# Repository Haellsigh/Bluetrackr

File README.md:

# Bluetrackr

Bluetrackr is a head tracking device. It allows you to track your head orientation & position in realtime. It's mainly used in games such as Elite Dangerous, Star Citizen, Flight simulators, etc to simulate head movement in a cockpit.

## Progress
prototype-v1: There was an unknown problem with the SPI bus. Might be because there are two devices on the same SPI bus?
prototype-v2: Ordered, waiting for parts.

Everything below is for v2.

### Transmitter schematic:

### Transmitter PCB:

### Transmitter PCB 3D view:

## Prototypes

#### Soldered prototype-v1

#### Board prototype-v2

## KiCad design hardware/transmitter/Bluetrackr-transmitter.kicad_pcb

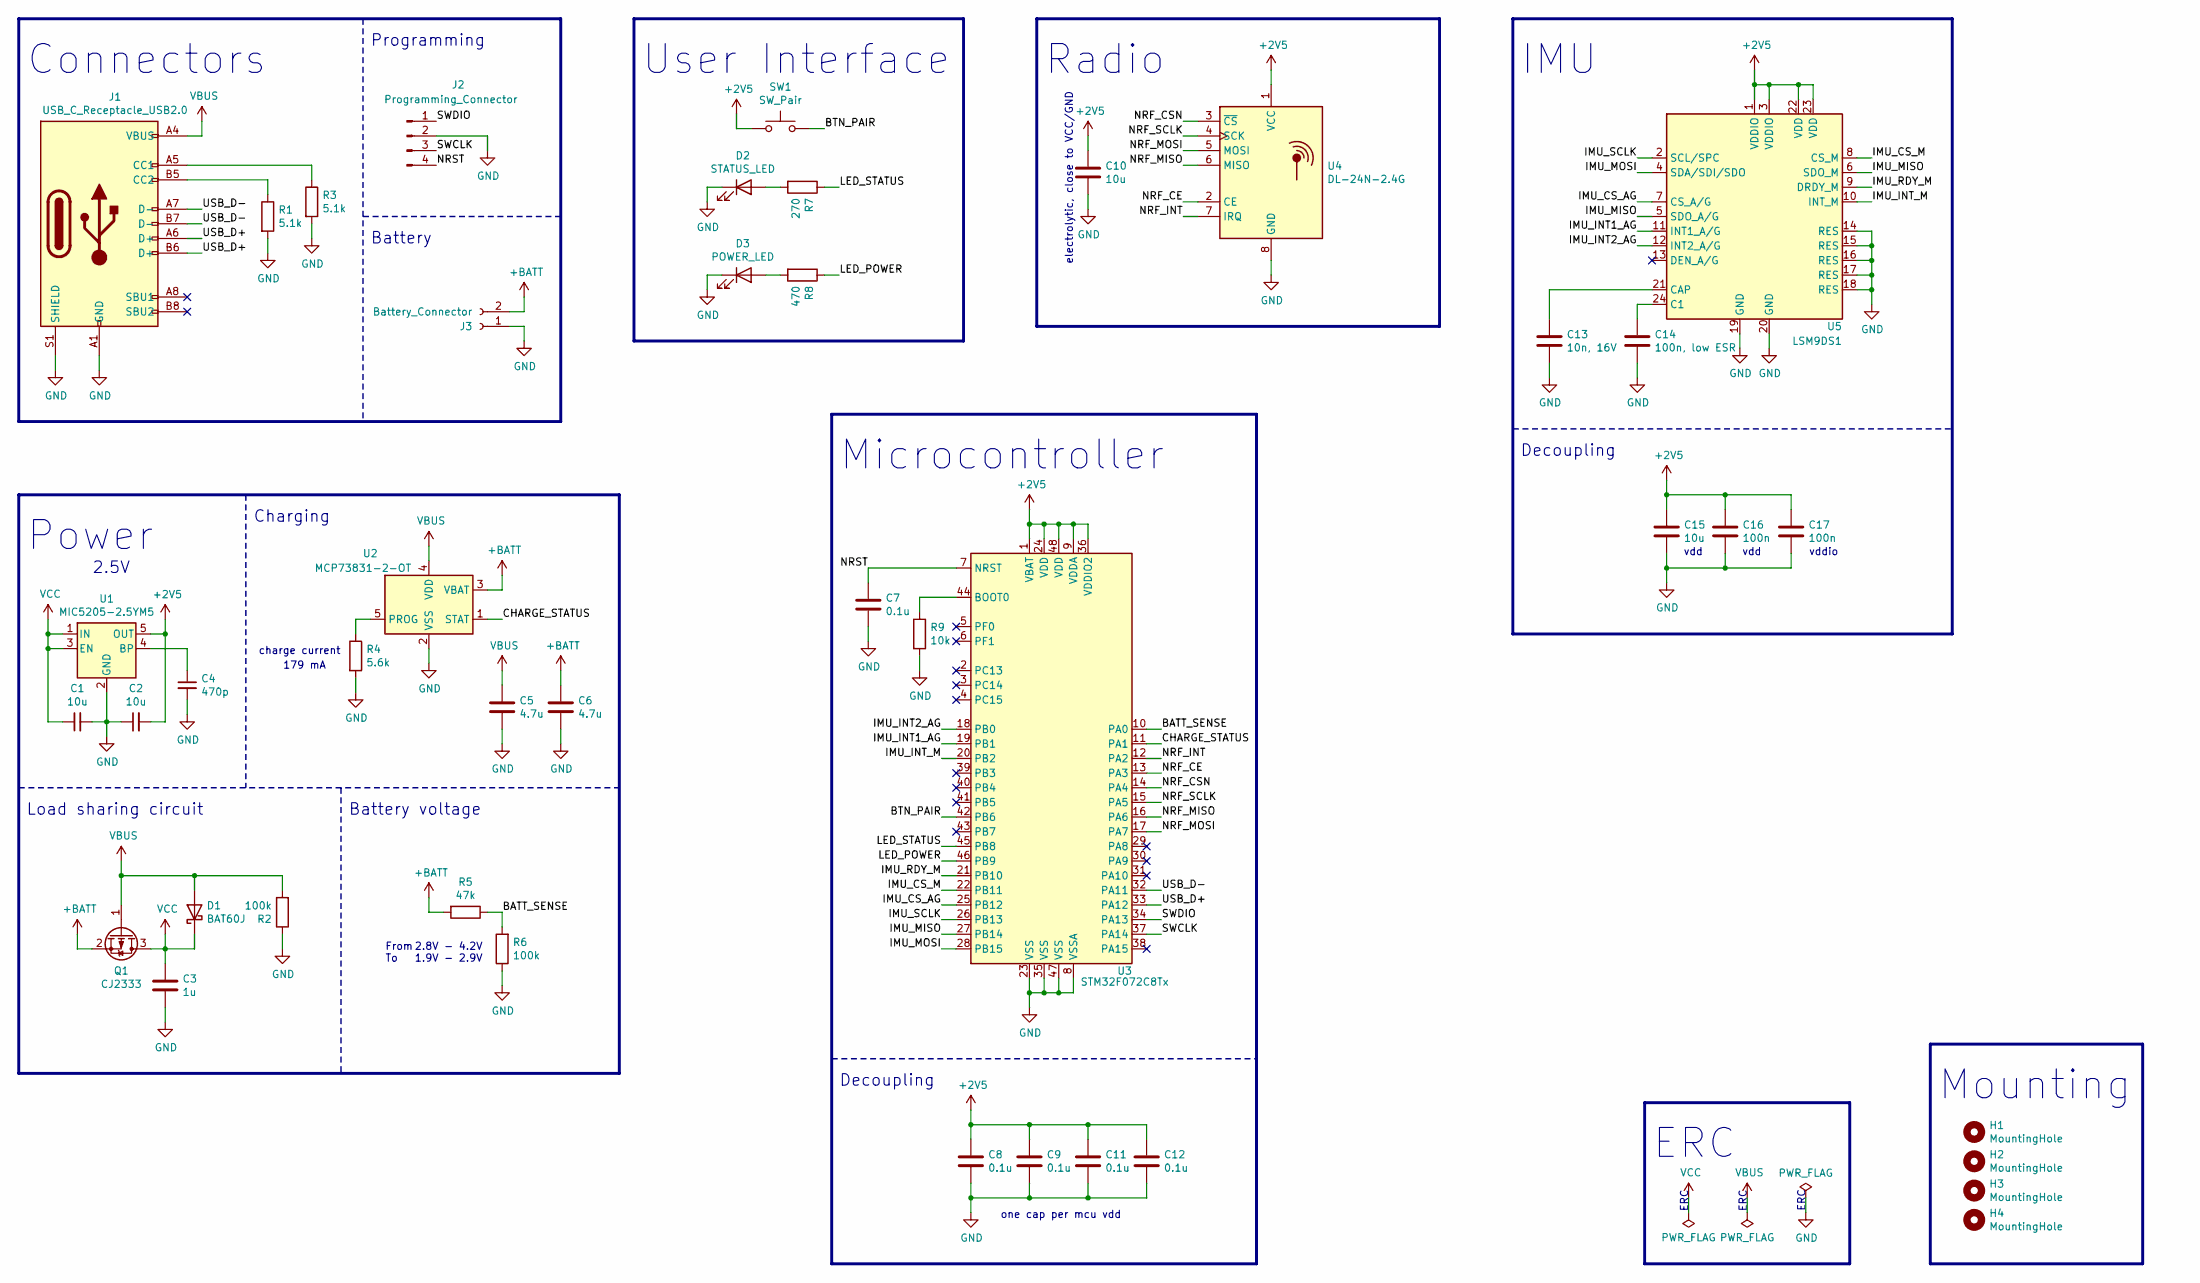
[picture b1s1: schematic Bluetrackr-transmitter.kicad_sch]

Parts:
C1, C2: 10u; C_0805_2012Metric_Pad1.15x1.40mm_HandSolder
C3: 1u; C_0805_2012Metric_Pad1.15x1.40mm_HandSolder
C4: 470p; C_0805_2012Metric_Pad1.15x1.40mm_HandSolder
C5, C6: 4.7u; C_0805_2012Metric_Pad1.15x1.40mm_HandSolder
C7, C8, C9, C11, C12: 0.1u; C_0805_2012Metric_Pad1.15x1.40mm_HandSolder
C10, C15: 10u; CP_Elec_3x5.3
C13: 10n, 16V; C_0805_2012Metric_Pad1.15x1.40mm_HandSolder
C14: 100n, low ESR; C_0805_2012Metric_Pad1.15x1.40mm_HandSolder
C16, C17: 100n; C_0805_2012Metric_Pad1.15x1.40mm_HandSolder
D1: BAT60J; D_SOD-323
D2: STATUS_LED; LED_1206_3216Metric_Pad1.42x1.75mm_HandSolder
D3: POWER_LED; LED_1206_3216Metric_Pad1.42x1.75mm_HandSolder
H1, H2, H3, H4: MountingHole; MountingHole_2.2mm_M2
J1: USB_C_Receptacle_USB2.0; USB_C_Receptacle_HRO_TYPE-C-31-M-12
J2: Programming_Connector; JST_B4B-ZR-SM4-TF
J3: Battery_Connector; JST_S2B-ZR-SM4A-TF
Q1: CJ2333; SOT-23
R1, R3: 5.1k; R_0805_2012Metric_Pad1.15x1.40mm_HandSolder
R2, R6: 100k; R_0805_2012Metric_Pad1.15x1.40mm_HandSolder
R4: 5.6k; R_0805_2012Metric_Pad1.15x1.40mm_HandSolder
R5: 47k; R_0805_2012Metric_Pad1.15x1.40mm_HandSolder
R7: 270; R_0805_2012Metric_Pad1.15x1.40mm_HandSolder
R8: 470; R_0805_2012Metric_Pad1.15x1.40mm_HandSolder
R9: 10k; R_0805_2012Metric_Pad1.15x1.40mm_HandSolder
SW1: SW_Pair; SW_PUSH_6mm_H9.5mm
U1: MIC5205-2.5YM5; SOT-23-5
U2: MCP73831-2-OT; SOT-23-5
U3: STM32F072C8Tx; LQFP-48_7x7mm_P0.5mm
U4: DL-24N-2.4G
U5: LSM9DS1; LGA-24L_3x3.5mm_P0.43mm

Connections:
+2V5: C2.2, C8.1, C9.1, C10.1, C11.1, C12.1, C15.1, C16.1, C17.1, SW1.1, U1.5 (OUT), U3.1 (VBAT), U3.9 (VDDA), U3.24 (VDD), U3.36 (VDDIO2), U3.48 (VDD), U4.1 (VCC), U5.1 (VDDIO), U5.3 (VDDIO), U5.22 (VDD), U5.23 (VDD)
+BATT: C6.1, J3.2, Q1.2 (S), R5.2, U2.3 (VBAT)
/BATT_SENSE: R5.1, R6.2, U3.10 (PA0)
/BTN_PAIR: SW1.2, U3.42 (PB6)
/CHARGE_STATUS: U2.1 (STAT), U3.11 (PA1)
/IMU_CS_AG: U3.25 (PB12), U5.7 (CS_A/G)
/IMU_CS_M: U3.22 (PB11), U5.8 (CS_M)
/IMU_INT1_AG: U3.19 (PB1), U5.11 (INT1_A/G)
/IMU_INT2_AG: U3.18 (PB0), U5.12 (INT2_A/G)
/IMU_INT_M: U3.20 (PB2), U5.10 (INT_M)
/IMU_MISO: U3.27 (PB14), U5.5 (SDO_A/G), U5.6 (SDO_M)
/IMU_MOSI: U3.28 (PB15), U5.4 (SDA/SDI/SDO)
/IMU_RDY_M: U3.21 (PB10), U5.9 (DRDY_M)
/IMU_SCLK: U3.26 (PB13), U5.2 (SCL/SPC)
/LED_POWER: R8.1, U3.46 (PB9)
/LED_STATUS: R7.1, U3.45 (PB8)
/NRF_CE: U3.13 (PA3), U4.2 (CE)
/NRF_CSN: U3.14 (PA4), U4.3 (~CS)
/NRF_INT: U3.12 (PA2), U4.7 (IRQ)
/NRF_MISO: U3.16 (PA6), U4.6 (MISO)
/NRF_MOSI: U3.17 (PA7), U4.5 (MOSI)
/NRF_SCLK: U3.15 (PA5), U4.4 (SCK)
/NRST: C7.1, J2.4, U3.7 (NRST)
/SWCLK: J2.3, U3.37 (PA14)
/SWDIO: J2.1, U3.34 (PA13)
/USB_D+: J1.A6 (D+), J1.B6 (D+), U3.33 (PA12)
/USB_D-: J1.A7 (D-), J1.B7 (D-), U3.32 (PA11)
GND: C1.2, C2.1, C3.2, C4.2, C5.2, C6.2, C7.2, C8.2, C9.2, C10.2, C11.2, C12.2, C13.2, C14.2, C15.2, C16.2, C17.2, D2.1 (K), D3.1 (K), J1.A1 (GND), J1.A12 (GND), J1.B1 (GND), J1.B12 (GND), J1.S1 (SHIELD), J2.2, J3.1, R1.2, R2.1, R3.2, R4.2, R6.1, R9.2, U1.2 (GND), U2.2 (VSS), U3.8 (VSSA), U3.23 (VSS), U3.35 (VSS), U3.47 (VSS), U4.8 (GND), U5.14 (RES), U5.15 (RES), U5.16 (RES), U5.17 (RES), U5.18 (RES), U5.19 (GND), U5.20 (GND)
unnamed: C4.1, U1.4 (BP)
unnamed: C13.1, U5.21 (CAP)
unnamed: C14.1, U5.24 (C1)
unnamed: D2.2 (A), R7.2
unnamed: D3.2 (A), R8.2
unnamed: J1.A5 (CC1), R3.1
unnamed: J1.B5 (CC2), R1.1
unnamed: R4.1, U2.5 (PROG)
unnamed: R9.1, U3.44 (BOOT0)
VBUS: C5.1, D1.2 (A), J1.A4 (VBUS), J1.A9 (VBUS), J1.B4 (VBUS), J1.B9 (VBUS), Q1.1 (G), R2.2, U2.4 (VDD)
VCC: C1.1, C3.1, D1.1 (K), Q1.3 (D), U1.1 (IN), U1.3 (EN)

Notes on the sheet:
Connectors
Power
Load sharing circuit
2.5V
Charging
179 mA
charge current
Battery voltage
Programming
Battery
From To
2.8V - 4.2V 1.9V - 2.9V
User Interface
Microcontroller
Decoupling
one cap per mcu vdd
Radio
electrolytic, close to VCC/GND
IMU
ERC
vdd
vddio
Mounting

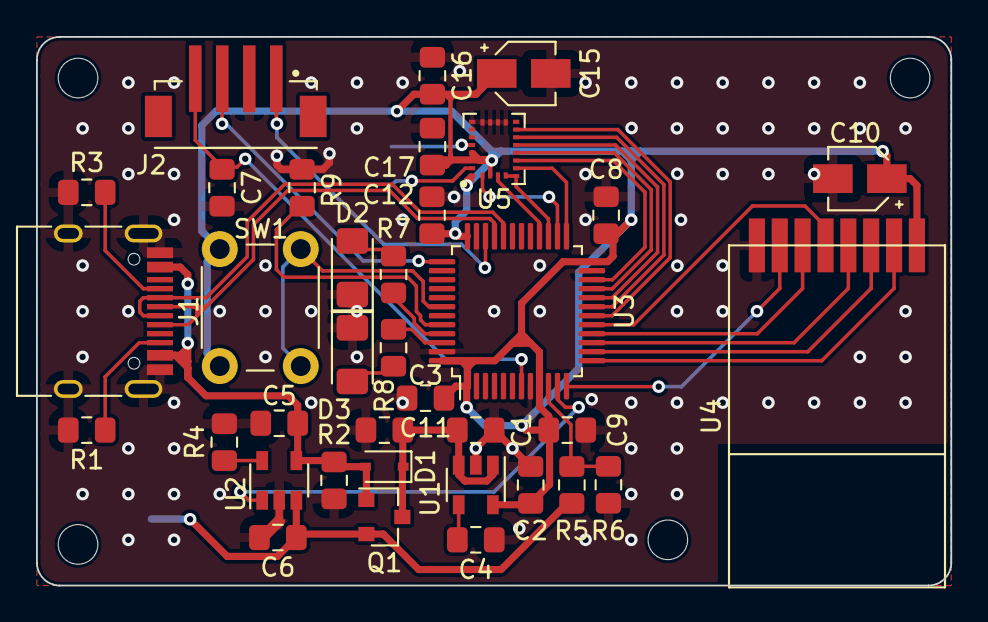
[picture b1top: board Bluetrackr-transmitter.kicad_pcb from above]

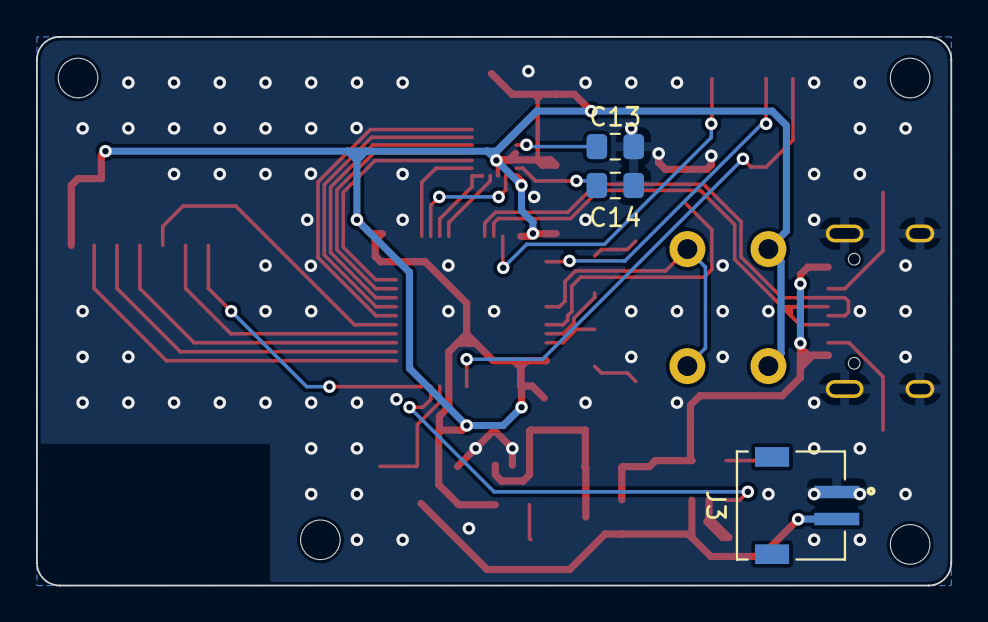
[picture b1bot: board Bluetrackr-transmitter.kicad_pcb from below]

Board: 2 copper layers, 50.8 x 30.5 mm, 43 parts (3 on the bottom side), 39 nets.

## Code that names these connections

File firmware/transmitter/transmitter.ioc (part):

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Mcu.Name=STM32F072C(8-B)Tx
Mcu.Package=LQFP48
Mcu.UserName=STM32F072C8Tx
PA0.GPIOParameters=GPIO_Label
PA0.GPIO_Label=BATT_SENSE
PA0.Mode=IN0
PA0.Signal=ADC_IN0
PA1.GPIOParameters=GPIO_Label
PA1.GPIO_Label=CHARGE_STATUS
PA1.Signal=GPIO_Input
PA11.Mode=Device
PA11.Signal=USB_DM
PA12.Mode=Device
PA12.Signal=USB_DP
PA13.Mode=Serial_Wire
PA13.Signal=SYS_SWDIO
PA14.Mode=Serial_Wire
PA14.Signal=SYS_SWCLK
PA2.GPIOParameters=GPIO_Label
PA2.GPIO_Label=NRF_INT
PA2.Signal=GPXTI2
PA3.GPIOParameters=GPIO_Label
PA3.GPIO_Label=NRF_CE
PA3.Signal=GPIO_Output
PA4.GPIOParameters=GPIO_Label
PA4.GPIO_Label=NRF_CSN
PA4.Signal=GPIO_Output
PA5.GPIOParameters=GPIO_Label
PA5.GPIO_Label=NRF_SCLK
PA5.Mode=Full_Duplex_Master
PA5.Signal=SPI1_SCK
PA6.GPIOParameters=GPIO_Label
PA6.GPIO_Label=NRF_MISO
PA6.Mode=Full_Duplex_Master
PA6.Signal=SPI1_MISO
PA7.GPIOParameters=GPIO_Label
PA7.GPIO_Label=NRF_MOSI
PA7.Mode=Full_Duplex_Master
PA7.Signal=SPI1_MOSI
PB0.GPIOParameters=GPIO_Label
PB0.GPIO_Label=IMU_INT2_AG
PB0.Signal=GPXTI0
PB1.GPIOParameters=GPIO_Label
PB1.GPIO_Label=IMU_INT1_AG
PB1.Signal=GPXTI1
PB10.GPIOParameters=GPIO_Label
PB10.GPIO_Label=IMU_RDY_M
PB10.Signal=GPIO_Input
PB11.GPIOParameters=GPIO_Label
PB11.GPIO_Label=IMU_CS_M
PB11.Signal=GPIO_Output
PB12.GPIOParameters=GPIO_Label
PB12.GPIO_Label=IMU_CS_AG
PB12.Signal=GPIO_Output
PB13.GPIOParameters=GPIO_Label
PB13.GPIO_Label=IMU_SCLK
PB13.Mode=Full_Duplex_Master
PB13.Signal=SPI2_SCK
PB14.GPIOParameters=GPIO_Label
PB14.GPIO_Label=IMU_MISO
PB14.Mode=Full_Duplex_Master
PB14.Signal=SPI2_MISO
PB15.GPIOParameters=GPIO_Label
PB15.GPIO_Label=IMU_MOSI
PB15.Mode=Full_Duplex_Master
PB15.Signal=SPI2_MOSI
PB6.GPIOParameters=GPIO_PuPd,GPIO_Label
PB6.GPIO_Label=BTN_PAIR
PB6.GPIO_PuPd=GPIO_PULLDOWN
PB6.Signal=GPIO_Input
PB8.GPIOParameters=GPIO_Label
PB8.GPIO_Label=LED_STATUS
PB8.Signal=GPIO_Output
PB9.GPIOParameters=GPIO_Label
PB9.GPIO_Label=LED_POWER
PB9.Signal=GPIO_Analog
RCC.SYSCLKFreq_VALUE=48000000
RCC.SYSCLKSource=RCC_SYSCLKSOURCE_PLLCLK
board=custom

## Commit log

2019-10-16 Add transmitter hardware project
2019-10-16 Remove pull down resistor on button
2019-10-16 Add base transmitter firmware project
2019-10-16 Ignore built files
2019-10-16 Finish transmitter schematic, pass DRC
2019-10-16 Layout the transmitter pcb
2019-10-16 Add progress images
2019-10-16 Add progress to README
2019-10-16 Update PCB rules
2019-10-16 Begin routing transmitter pcb
2019-10-17 Finished transmitter routing
2019-10-18 First working test: read MPU9250 values & output to serial
2019-10-25 Update firmware
2019-11-05 Begin receiver schematic
2019-11-21 Received, assembled, programmed the first working prototype of the transmitter
2019-11-24 Replace global labels with net labels
2019-11-24 Replace the unused programming pin with NRST to support stlink reset
2019-11-24 Updated changelog with commits
2019-11-27 Begin working on the blt library
2019-12-06 Moved the common libraries to a common folder
2019-12-06 Add hardware gitignore
2019-12-20 Add nRF24L01 v2 doc
2019-12-20 Fix nRF24 implementation a bit, still not working
2020-01-15 Hardware does not seem to work yet on the receiver side.
2020-01-17 Update transmitter schematic
2020-05-31 Use CMake to build the firmware
2020-06-02 Maybe it will work someday
2020-06-02 The current hardware doesn't seem to work
2020-06-04 Redesign most of the transmitter hardware
    Changes:
    - Switch to KiCad 6 files
    - Change microcontroller to STM32F030R8T6
    - Use two SPI buses, one for each device
    - Replace TP4056 module for a custom solution with:
    - USB Type-C USB 2.0 receptacle
2020-06-04 Remove changelog for now
2020-06-04 Fix not connected errors on ERC
2020-06-04 Update firmware and hardware gitignore
2020-06-04 Add board basic dimensions 5x3cm
2020-06-04 Rename schematic file
2020-06-04 Crop transmitter schematic
2020-06-04 Plot transmitter schematic again
2020-06-04 Update transmitter schematic pdf
2020-06-04 Change level shifting resistors to 10k
2020-06-04 Add transmitter schematic
2020-06-04 Changed regulator from 3.3V to 2.5V
2020-06-10 Began routing the pcb
2020-06-10 Replace nRF24 breakout with DL-24N nRF24 smd module
2020-06-10 Update hardware docs
2020-06-10 Replace ICM-20948 with LSM9DS1, removes 1.8V supply and level shifters
2020-06-10 Annotate schematic
2020-06-10 Remove pcb
2020-06-10 Finish schematic with new Radio & IMU
2020-06-10 Place mounting holes, usb connector, mcu and radio
2020-06-10 Setup board rules
2020-06-10 Move mounting holes silkscreen to fab layer
2020-06-10 Changed MCU to IMU pins
2020-06-10 Placed MCU and IMU
2020-06-10 Change MCU to STM32F072C8T6 for USB
2020-06-10 Reset and run bugged KiCad 5.99 ERC
2020-06-10 Add basic transmitter pcb with main ICs laid
2020-06-10 Place Power components
2020-06-11 Place CC1 and CC2 for USB
2020-06-11 Place LEDs
2020-06-11 Place BOOT0 resistor
2020-06-11 Change connectors to ZH SMD versions
2020-06-11 Add 3D models to JST ZH connectors
2020-06-11 Begin routing
2020-06-11 Routed USB, SPI tracks
2020-06-11 Finish routing the transmitter, add DL-24N module step file
2020-06-11 Correct some power traces
2020-06-11 Moved IMU interrupt lines further away
2020-06-11 Final PCB, ordered at JLCPCB
2020-06-11 Reset solder mask clearancec
2020-06-11 Plot gerbers and drill files
2020-06-11 Update plot settings
2020-06-12 Update schematic
2020-06-12 Update gitignores
2020-06-12 Update README images
2020-06-12 Remove ignored file
2020-06-12 Changed targets for testing to F303K8
2020-06-12 Switch target to F103 bluepill and add USB CDC
2020-06-14 Quick USB CDC test
2020-06-14 Begin removing CMake, use Platormio
2020-06-14 Add simple debug library for F303K8 via VCP UART
2020-06-14 Working PlatformIO integration
2020-06-14 Switched receiver to Platformio
2020-06-15 Fix nRF24 code on transmitter side
2020-06-18 Add transmitter board v1 and v2 images
2020-06-18 Update readme with prototypes
2020-06-18 Add goal
2020-06-20 Setup a typesafe register manipulation system entirely based on types
2020-06-26 Finish typesafe version prototype of the nRF24 library
2020-06-26 Fixed a pin toggling error in blt::gpio
2020-06-27 Working data transmission between a transmitter and a receiver
2020-06-27 Enable Usb Clock Recovery System (CRS) on the receiver side
2020-07-05 Commit before prototype programming
2020-07-07 Add HID joystick driver base
2020-07-07 USB HID custom virtual reality joystick with 3 axes implemented
2020-09-01 Update KiCad version
2020-09-01 Setup USB DFU updates on the transmitter on button press
2020-09-06 Describe all the lsm9ds1 accel and gyro registers using a new typesafe method
2020-09-08 Finished base lsm9ds1 library with a working wireless transmission of acc & gyro data
2020-11-16 Big update I forgot to push...
2020-12-21 Update formatting of kicad files
